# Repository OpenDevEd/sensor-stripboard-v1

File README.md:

# sensor-stripboard-v1
This stripboard is meant to be used with this case: https://github.com/OpenDevEd/case-for-pico-datalogger-rev0.98

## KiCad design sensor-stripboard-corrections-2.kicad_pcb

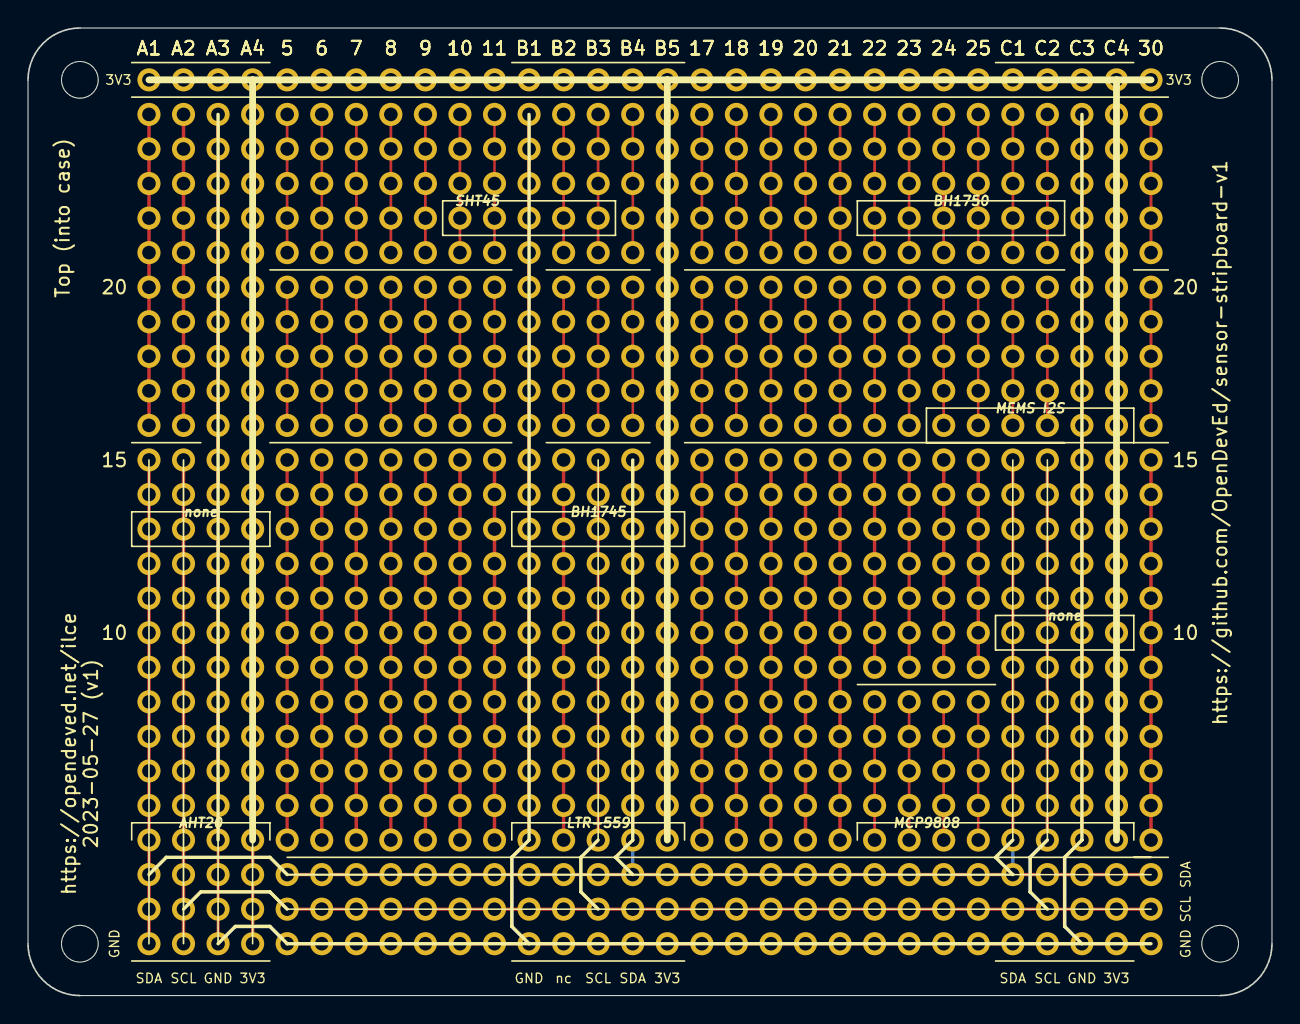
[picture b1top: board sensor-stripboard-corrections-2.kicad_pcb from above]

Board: 2 copper layers, 91.4 x 71.1 mm, 30 parts (0 on the bottom side), 4 nets.

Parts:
5, 6, 7, 8, 9, 10, 11, 17, 18, 19, 20, 21, 22, 23, 24, 25, 30: P; PinHeader_1x26_P2.54mm_Vertical-Custom
A1, A2, A3, A4: P; PinHeader_1x26_P2.54mm_Vertical-Custom
B1, B2, B3, B4, B5: P; PinHeader_1x26_P2.54mm_Vertical-Custom
C1, C2, C3, C4: P; PinHeader_1x26_P2.54mm_Vertical-Custom

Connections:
3V3: 5.1, 6.1, 7.1, 8.1, 9.1, 10.1, 11.1, 17.1, 18.1, 19.1, 20.1, 21.1, 22.1, 23.1, 24.1, 25.1, 30.1, A1.1, A2.1, A3.1, A4.1, A4.2, A4.3, A4.4, A4.5, A4.6, A4.7, A4.8, A4.9, A4.10, A4.11, A4.12, A4.13, A4.14, A4.15, A4.16, A4.17, A4.18, A4.19, A4.20, A4.21, A4.22, A4.23, A4.24, A4.25, A4.26, B1.1, B2.1, B3.1, B4.1, B5.1, B5.2, B5.3, B5.4, B5.5, B5.6, B5.7, B5.8, B5.9, B5.10, B5.11, B5.12, B5.13, B5.14, B5.15, B5.16, B5.17, B5.18, B5.19, B5.20, B5.21, B5.22, B5.23, C1.1, C2.1, C3.1, C4.1, C4.2, C4.3, C4.4, C4.5, C4.6, C4.7, C4.8, C4.9, C4.10, C4.11, C4.12, C4.13, C4.14, C4.15, C4.16, C4.17, C4.18, C4.19, C4.20, C4.21, C4.22, C4.23
GND: 5.26, 6.26, 7.26, 8.26, 9.26, 10.26, 11.26, 17.26, 18.26, 19.26, 20.26, 21.26, 22.26, 23.26, 24.26, 25.26, 30.26, A3.2, A3.3, A3.4, A3.5, A3.6, A3.7, A3.8, A3.9, A3.10, A3.11, A3.12, A3.13, A3.14, A3.15, A3.16, A3.17, A3.18, A3.19, A3.20, A3.21, A3.22, A3.23, A3.24, A3.25, A3.26, B1.2, B1.3, B1.4, B1.5, B1.6, B1.7, B1.8, B1.9, B1.10, B1.11, B1.12, B1.13, B1.14, B1.15, B1.16, B1.17, B1.18, B1.19, B1.20, B1.21, B1.22, B1.23, B1.26, B2.26, B3.26, B4.26, B5.26, C1.26, C2.26, C3.2, C3.3, C3.4, C3.5, C3.6, C3.7, C3.8, C3.9, C3.10, C3.11, C3.12, C3.13, C3.14, C3.15, C3.16, C3.17, C3.18, C3.19, C3.20, C3.21, C3.22, C3.23, C3.26, C4.26
SCL: 5.25, 6.25, 7.25, 8.25, 9.25, 10.25, 11.25, 17.25, 18.25, 19.25, 20.25, 21.25, 22.25, 23.25, 24.25, 25.25, 30.25, A2.12, A2.13, A2.14, A2.15, A2.16, A2.17, A2.18, A2.19, A2.20, A2.21, A2.22, A2.23, A2.24, A2.25, A2.26, B1.25, B2.25, B3.12, B3.13, B3.14, B3.15, B3.16, B3.17, B3.18, B3.19, B3.20, B3.21, B3.22, B3.23, B3.25, B4.25, B5.25, C1.25, C2.12, C2.13, C2.14, C2.15, C2.16, C2.17, C2.18, C2.19, C2.20, C2.21, C2.22, C2.23, C2.25, C3.25, C4.25
SDA: 5.24, 6.24, 7.24, 8.24, 9.24, 10.24, 11.24, 17.24, 18.24, 19.24, 20.24, 21.24, 22.24, 23.24, 24.24, 25.24, 30.24, A1.12, A1.13, A1.14, A1.15, A1.16, A1.17, A1.18, A1.19, A1.20, A1.21, A1.22, A1.23, A1.24, A1.25, A1.26, B1.24, B2.24, B3.24, B4.12, B4.13, B4.14, B4.15, B4.16, B4.17, B4.18, B4.19, B4.20, B4.21, B4.22, B4.23, B4.24, B5.24, C1.12, C1.13, C1.14, C1.15, C1.16, C1.17, C1.18, C1.19, C1.20, C1.21, C1.22, C1.23, C1.24, C2.24, C3.24, C4.24
